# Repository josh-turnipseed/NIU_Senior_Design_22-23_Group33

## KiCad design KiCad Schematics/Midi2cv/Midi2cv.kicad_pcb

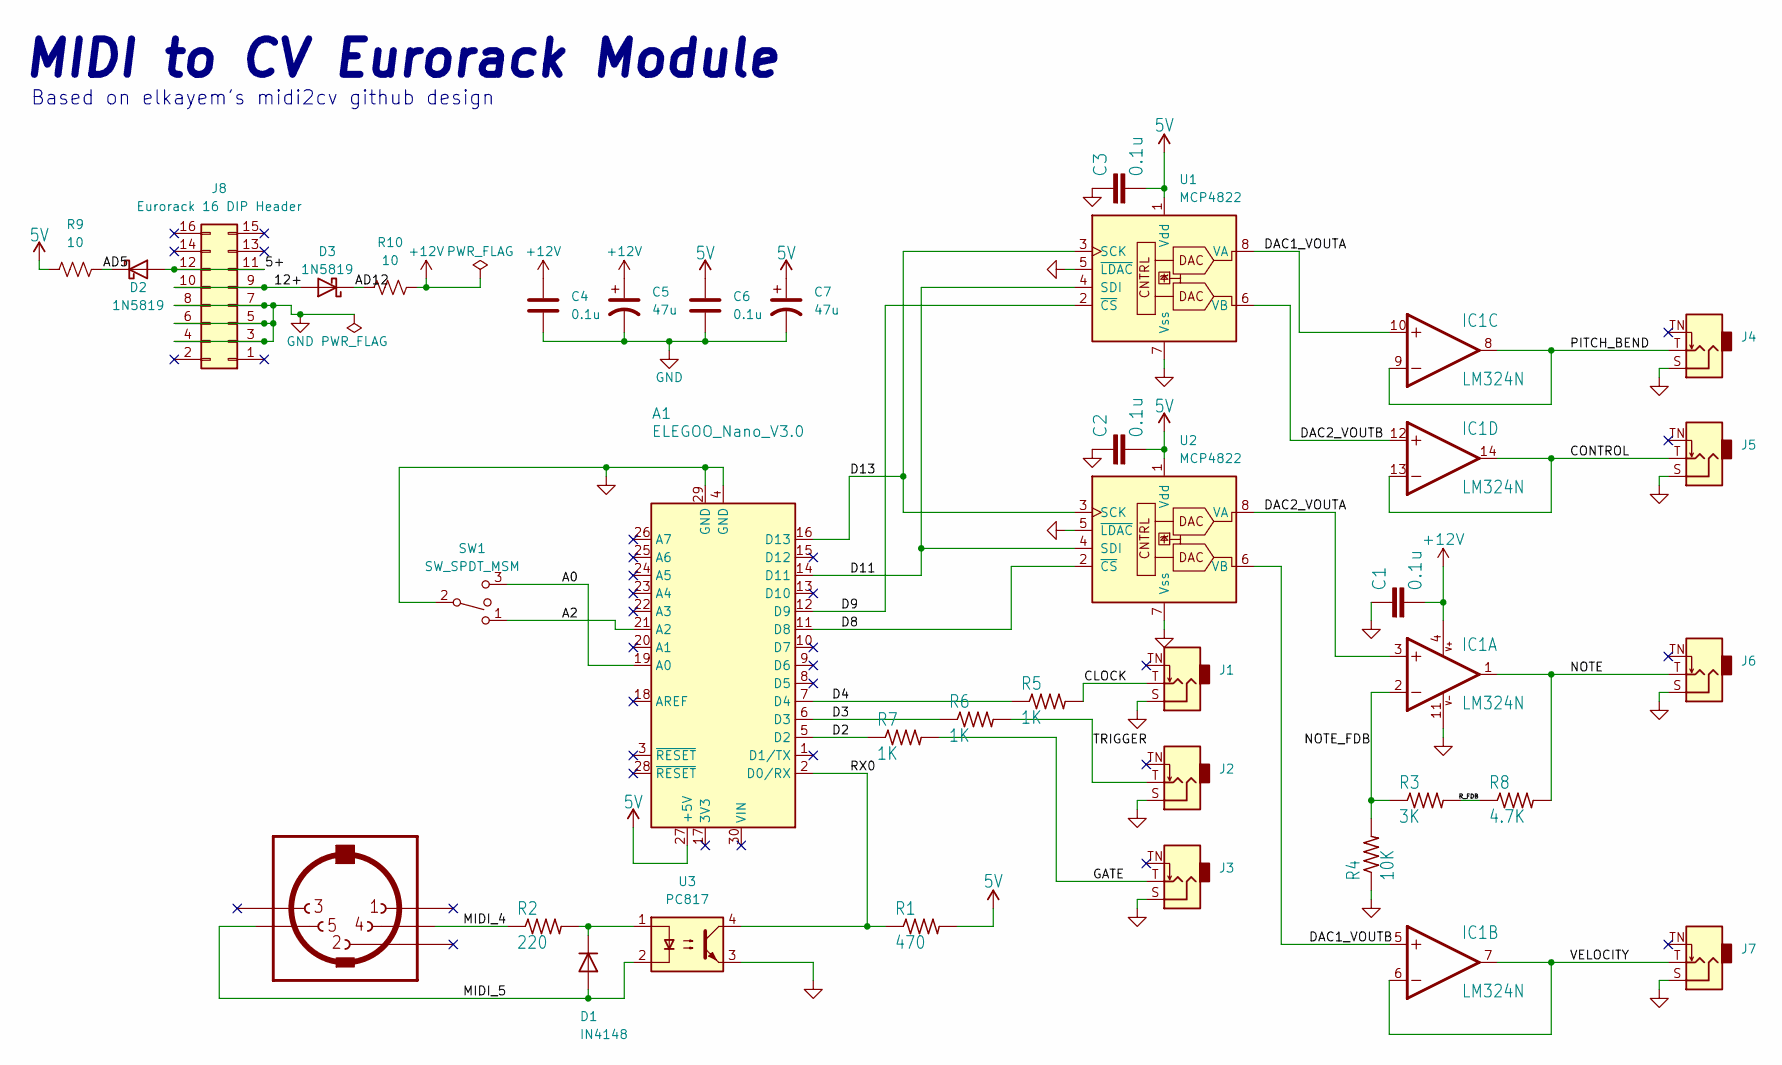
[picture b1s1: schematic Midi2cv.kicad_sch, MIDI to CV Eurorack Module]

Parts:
A1: ELEGOO_Nano_V3.0; Arduino_Nano
C1, C2, C3, C4, C6: 0.1u; C_Disc_D4.7mm_W2.5mm_P5.00mm
C5, C7: 47u; CP_Radial_D4.0mm_P1.50mm
D1: IN4148; D_DO-35_SOD27_P7.62mm_Horizontal
D2, D3: 1N5819; D_DO-41_SOD81_P10.16mm_Horizontal
IC1: LM324N; DIP-14_W7.62mm
J1: Clock; Jack_3.5mm_QingPu_WQP-PJ398SM_Vertical_CircularHoles
J2: Trigger; Jack_3.5mm_QingPu_WQP-PJ398SM_Vertical_CircularHoles
J3: Gate; Jack_3.5mm_QingPu_WQP-PJ398SM_Vertical_CircularHoles
J4: Pitch Bend; Jack_3.5mm_QingPu_WQP-PJ398SM_Vertical_CircularHoles
J5: Continuous Control; Jack_3.5mm_QingPu_WQP-PJ398SM_Vertical_CircularHoles
J6: Note; Jack_3.5mm_QingPu_WQP-PJ398SM_Vertical_CircularHoles
J7: Velocity; Jack_3.5mm_QingPu_WQP-PJ398SM_Vertical_CircularHoles
J8: Eurorack 16 DIP Header; Eurorack_16_pin_header
R1: 470; R_Axial_DIN0207_L6.3mm_D2.5mm_P7.62mm_Horizontal
R2: 220; R_Axial_DIN0207_L6.3mm_D2.5mm_P7.62mm_Horizontal
R3: 3K; R_Axial_DIN0207_L6.3mm_D2.5mm_P7.62mm_Horizontal
R4: 10K; R_Axial_DIN0207_L6.3mm_D2.5mm_P7.62mm_Horizontal
R5, R6, R7: 1K; R_Axial_DIN0207_L6.3mm_D2.5mm_P7.62mm_Horizontal
R8: 4.7K; R_Axial_DIN0207_L6.3mm_D2.5mm_P7.62mm_Horizontal
R9, R10: 10; R_Axial_DIN0207_L6.3mm_D2.5mm_P7.62mm_Horizontal
SW1: SW_SPDT_MSM; SPDT toggle on-off-on
U1, U2: MCP4822; DIP-8_W7.62mm
U3: PC817; DIP-4_W7.62mm
U$1: MIDIJACK; CUI_SD-50BV

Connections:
5V: A1.27 (+5V), C2.2, C3.2, C6.2, C7.1, R1.2, R9.2, U1.1 (Vdd), U2.1 (Vdd)
+12V: C1.2, C4.2, C5.1, IC1.4 (V+), R10.1
/5+: D2.2 (A), J8.11, J8.12
/12+: D3.2 (A), J8.9, J8.10
/A0: A1.19 (A0), SW1.3
/A2: A1.21 (A2), SW1.1
/AD5: D2.1 (K), R9.1
/AD12: D3.1 (K), R10.2
/CLOCK: J1.T, R5.2
/CONTROL: IC1.13 (-IN), IC1.14 (OUT), J5.T
/D2: A1.5 (D2), R7.1
/D3: A1.6 (D3), R6.1
/D4: A1.7 (D4), R5.1
/D8: A1.11 (D8), U2.2 (~CS)
/D9: A1.12 (D9), U1.2 (~CS)
/D11: A1.14 (D11), U1.4 (SDI), U2.4 (SDI)
/D13: A1.16 (D13), U1.3 (SCK), U2.3 (SCK)
/DAC1_VOUTA: IC1.10 (+IN), U1.8 (VA)
/DAC1_VOUTB: IC1.5 (+IN), U2.6 (VB)
/DAC2_VOUTA: IC1.3 (+IN), U2.8 (VA)
/DAC2_VOUTB: IC1.12 (+IN), U1.6 (VB)
/GATE: J3.T, R7.2
/MIDI_4: R2.1, U$1.4
/MIDI_5: D1.2 (A), U3.2, U$1.5
/NOTE: IC1.1 (OUT), J6.T, R8.2
/NOTE_FDB: IC1.2 (-IN), R3.1, R4.2
/PITCH_BEND: IC1.8 (OUT), IC1.9 (-IN), J4.T
/RX0: A1.2 (D0/RX), R1.1, U3.4
/R_FDB: R3.2, R8.1
/TRIGGER: J2.T, R6.2
/VELOCITY: IC1.6 (-IN), IC1.7 (OUT), J7.T
GND: A1.4 (GND), A1.29 (GND), C1.1, C2.1, C3.1, C4.1, C5.2, C6.1, C7.2, IC1.11 (V-), J1.S, J2.S, J3.S, J4.S, J5.S, J6.S, J7.S, J8.3, J8.4, J8.5, J8.6, J8.7, J8.8, R4.1, SW1.2, U1.5 (~LDAC), U1.7 (Vss), U2.5 (~LDAC), U2.7 (Vss), U3.3
unnamed: D1.1 (K), R2.2, U3.1

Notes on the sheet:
Based on elkayem's midi2cv github design
MIDI to CV Eurorack Module

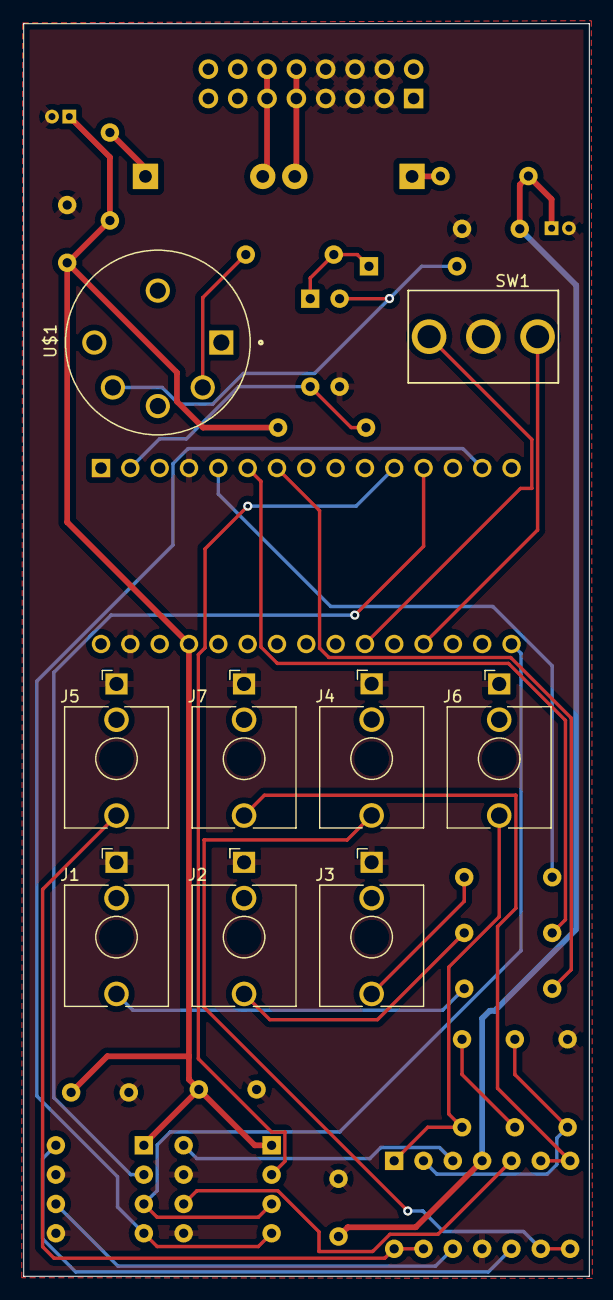
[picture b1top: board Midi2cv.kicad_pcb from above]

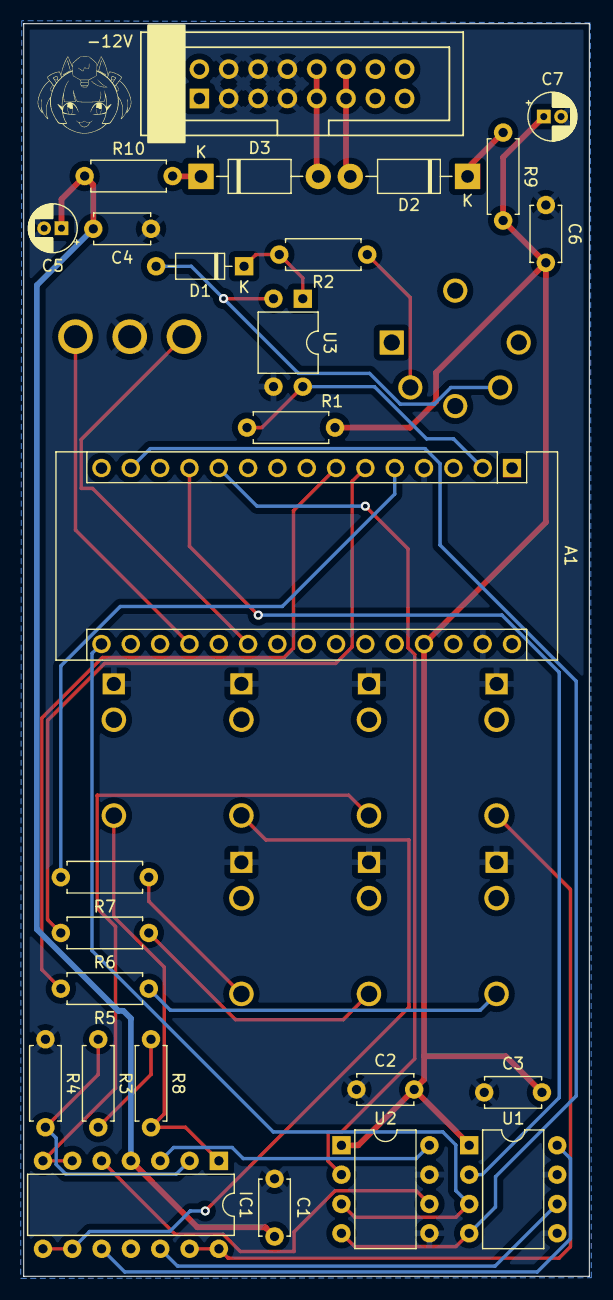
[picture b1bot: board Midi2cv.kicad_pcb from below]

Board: 2 copper layers, 49.0 x 108.5 mm, 35 parts (26 on the bottom side), 33 nets.

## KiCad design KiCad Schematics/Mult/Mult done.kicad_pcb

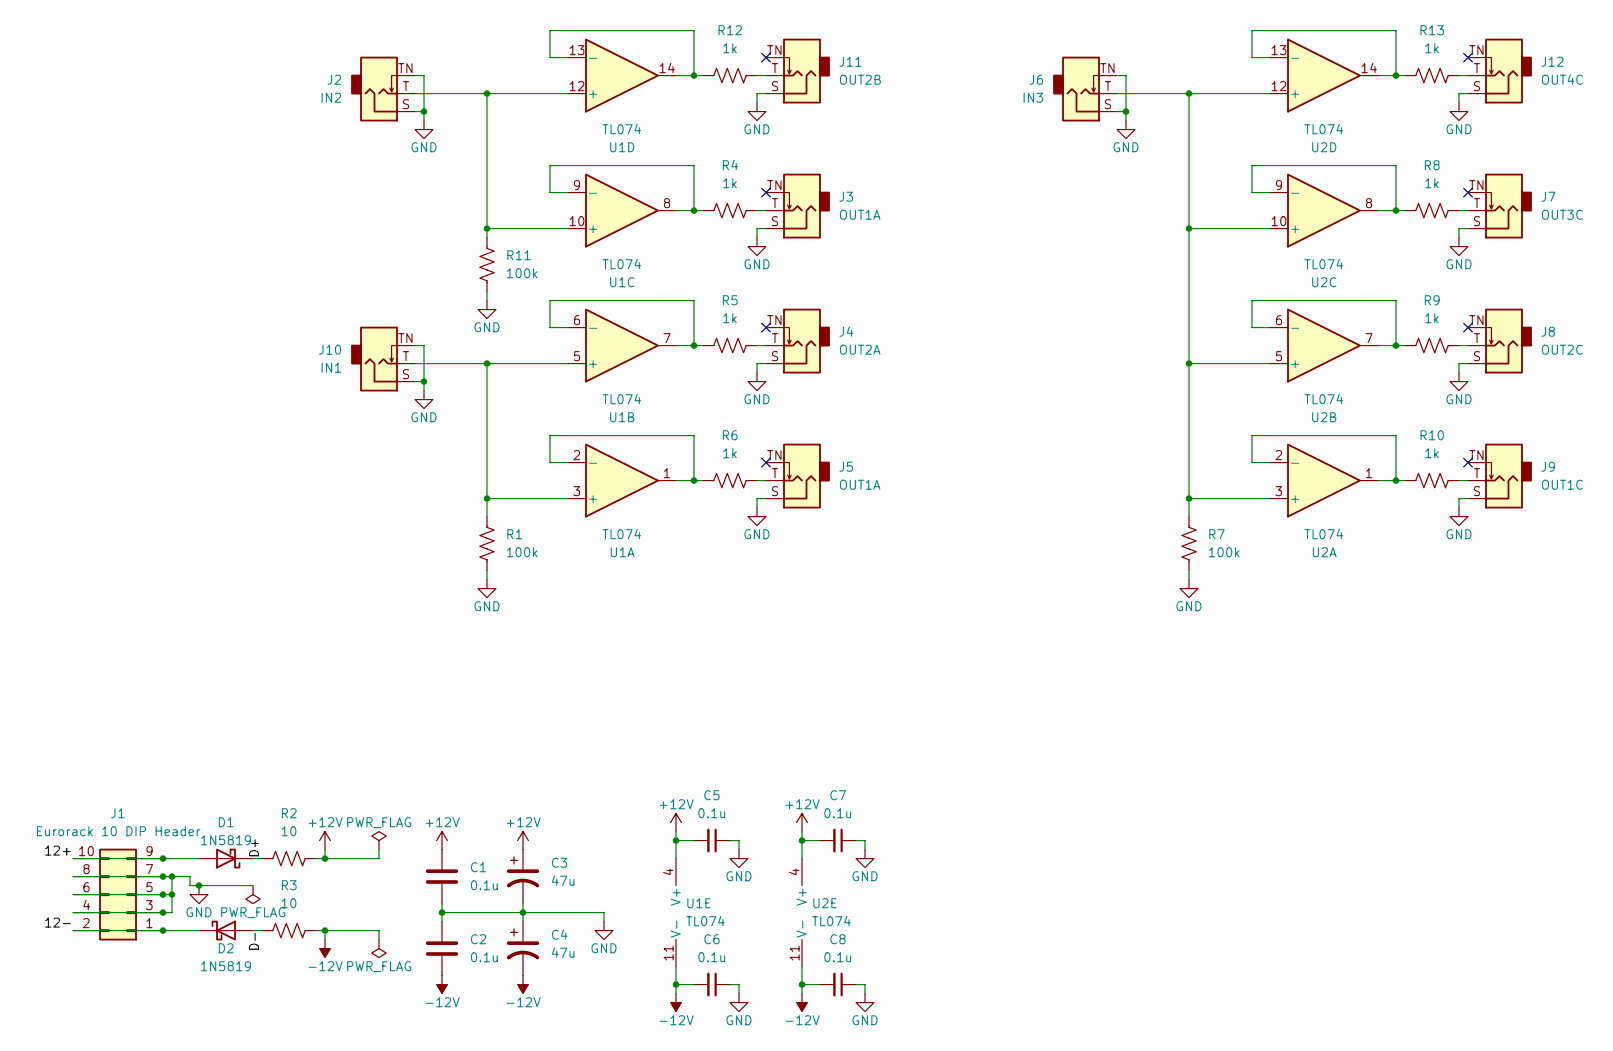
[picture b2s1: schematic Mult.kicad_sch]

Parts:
C1, C2, C5, C6, C7, C8: 0.1u; C_Disc_D4.7mm_W2.5mm_P5.00mm
C3, C4: 47u; CP_Radial_D4.0mm_P2.00mm
D1, D2: 1N5819; D_DO-41_SOD81_P10.16mm_Horizontal
J1: Eurorack 10 DIP Header; Eurorack_10_pin_header
J2: IN2; Jack_3.5mm_QingPu_WQP-PJ398SM_Vertical_CircularHoles
J3, J5: OUT1A; Jack_3.5mm_QingPu_WQP-PJ398SM_Vertical_CircularHoles
J4: OUT2A; Jack_3.5mm_QingPu_WQP-PJ398SM_Vertical_CircularHoles
J6: IN3; Jack_3.5mm_QingPu_WQP-PJ398SM_Vertical_CircularHoles
J7: OUT3C; Jack_3.5mm_QingPu_WQP-PJ398SM_Vertical_CircularHoles
J8: OUT2C; Jack_3.5mm_QingPu_WQP-PJ398SM_Vertical_CircularHoles
J9: OUT1C; Jack_3.5mm_QingPu_WQP-PJ398SM_Vertical_CircularHoles
J10: IN1; Jack_3.5mm_QingPu_WQP-PJ398SM_Vertical_CircularHoles
J11: OUT2B; Jack_3.5mm_QingPu_WQP-PJ398SM_Vertical_CircularHoles
J12: OUT4C; Jack_3.5mm_QingPu_WQP-PJ398SM_Vertical_CircularHoles
R1, R7, R11: 100k; R_Axial_DIN0207_L6.3mm_D2.5mm_P7.62mm_Horizontal
R2, R3: 10; R_Axial_DIN0207_L6.3mm_D2.5mm_P7.62mm_Horizontal
R4, R5, R6, R8, R9, R10, R12, R13: 1k; R_Axial_DIN0207_L6.3mm_D2.5mm_P7.62mm_Horizontal
U1, U2: TL074; DIP-14_W7.62mm

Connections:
+12V: C1.2, C3.1, C5.2, C7.2, R2.1, U1.4 (V+), U2.4 (V+)
-12V: C2.1, C4.2, C6.2, C8.2, R3.1, U1.11 (V-), U2.11 (V-)
/12+: D1.2 (A), J1.9, J1.10
/12-: D2.1 (K), J1.1, J1.2
/D+: D1.1 (K), R2.2
/D-: D2.2 (A), R3.2
GND: C1.1, C2.2, C3.2, C4.1, C5.1, C6.1, C7.1, C8.1, J1.3, J1.4, J1.5, J1.6, J1.7, J1.8, J2.S, J2.TN, J3.S, J4.S, J5.S, J6.S, J6.TN, J7.S, J8.S, J9.S, J10.S, J10.TN, J11.S, J12.S, R1.2, R7.2, R11.2
unnamed: J2.T, R11.1, U1.10 (+), U1.12 (+)
unnamed: J3.T, R4.2
unnamed: J4.T, R5.2
unnamed: J5.T, R6.2
unnamed: J6.T, R7.1, U2.3 (+), U2.5 (+), U2.10 (+), U2.12 (+)
unnamed: J7.T, R8.2
unnamed: J8.T, R9.2
unnamed: J9.T, R10.2
unnamed: J10.T, R1.1, U1.3 (+), U1.5 (+)
unnamed: J11.T, R12.2
unnamed: J12.T, R13.2
unnamed: R4.1, U1.8, U1.9 (-)
unnamed: R5.1, U1.6 (-), U1.7
unnamed: R6.1, U1.1, U1.2 (-)
unnamed: R8.1, U2.8, U2.9 (-)
unnamed: R9.1, U2.6 (-), U2.7
unnamed: R10.1, U2.1, U2.2 (-)
unnamed: R12.1, U1.13 (-), U1.14
unnamed: R13.1, U2.13 (-), U2.14

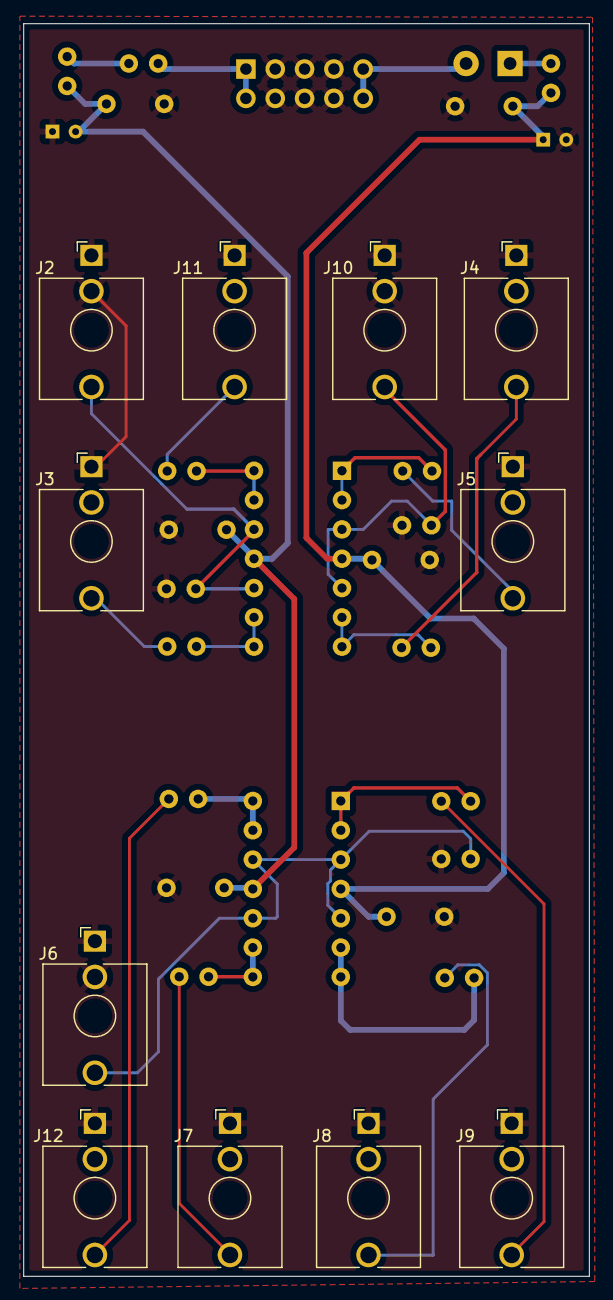
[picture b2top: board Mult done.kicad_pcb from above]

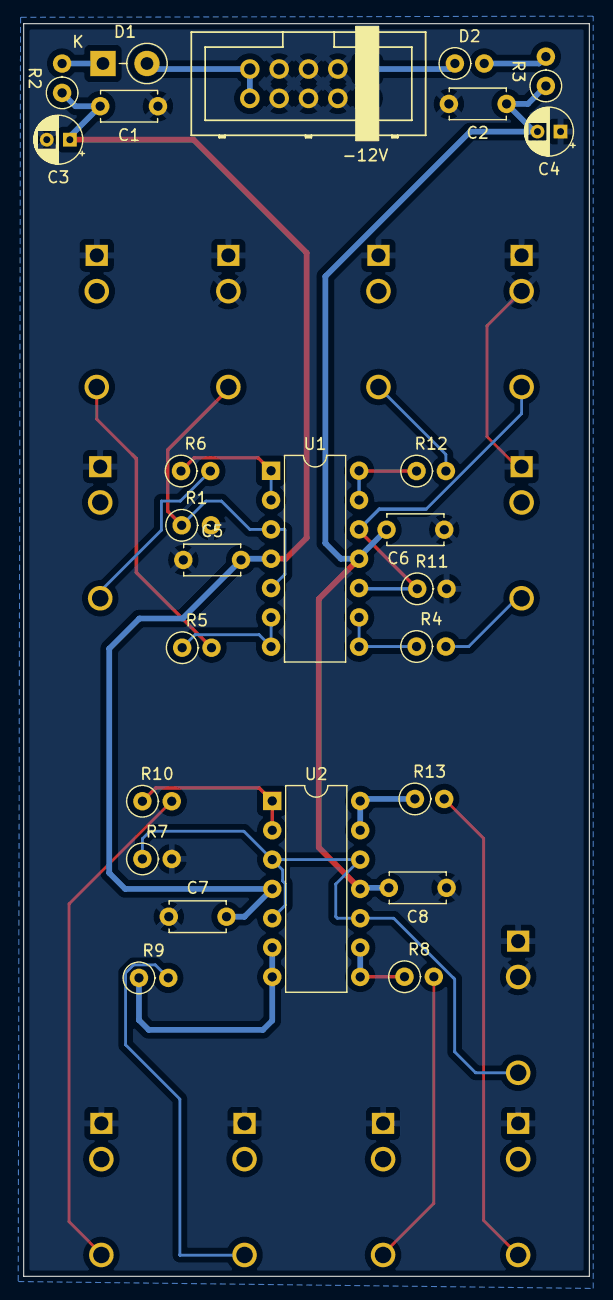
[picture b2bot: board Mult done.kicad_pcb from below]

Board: 2 copper layers, 49.0 x 108.5 mm, 37 parts (26 on the bottom side), 26 nets.

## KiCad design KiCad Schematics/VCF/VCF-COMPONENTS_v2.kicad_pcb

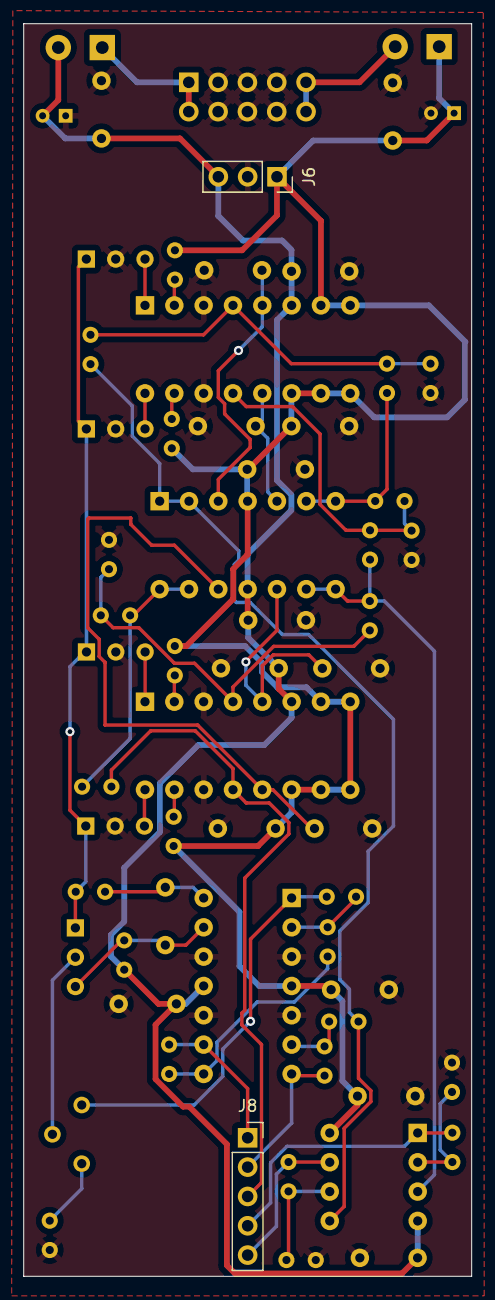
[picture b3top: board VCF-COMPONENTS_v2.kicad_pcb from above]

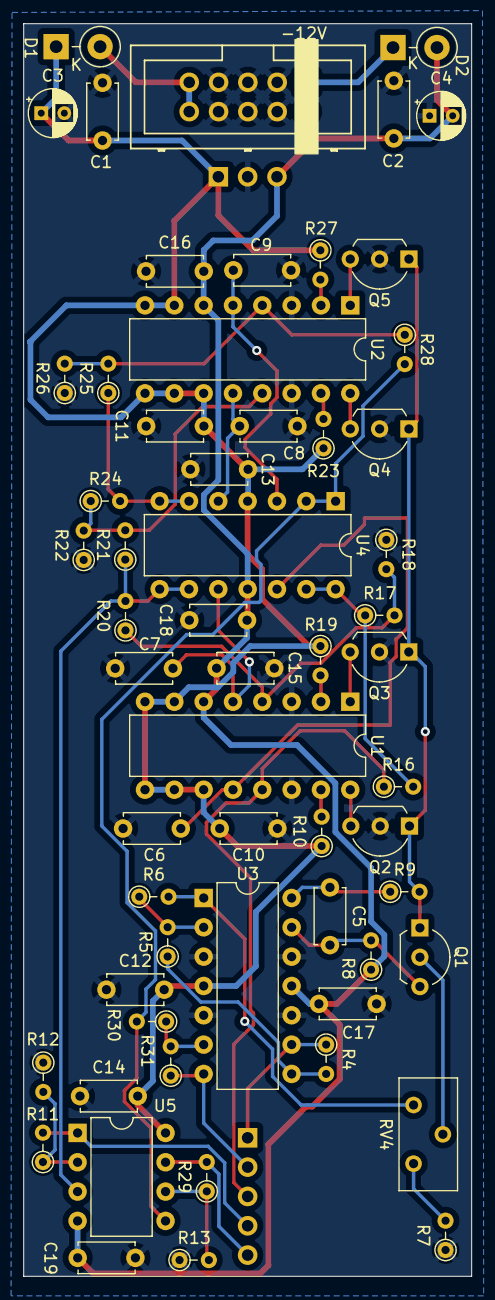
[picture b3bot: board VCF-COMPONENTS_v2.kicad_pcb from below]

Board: 2 copper layers, 38.8 x 108.5 mm, 61 parts (59 on the bottom side), 40 nets.

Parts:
C1, C2, C10, C11, C12, C13, C14, C15, C16, C17, C18, C19: 0.1u; C_Disc_D4.7mm_W2.5mm_P5.00mm
C3, C4: 47u; CP_Radial_D4.0mm_P2.00mm
C5: 20p; C_Disc_D4.7mm_W2.5mm_P5.00mm
C6, C7, C8, C9: 100p; C_Disc_D4.7mm_W2.5mm_P5.00mm
D1, D2: 1N5819; D_DO-41_SOD81_P3.81mm_Vertical_KathodeUp
J1: Eurorack 10 DIP Header; Eurorack_10_pin_header
J6: Comp1; PinSocket_1x03_P2.54mm_Vertical
J8: Comp2; PinSocket_1x05_P2.54mm_Vertical
Q1, Q2, Q3, Q4, Q5: 2N3906; TO-92L_Inline_Wide
R4, R5, R12, R13, R16, R17, R20, R21, R24, R25, R28, R31: 100k; R_Axial_DIN0204_L3.6mm_D1.6mm_P2.54mm_Vertical
R6: 1.87k; R_Axial_DIN0204_L3.6mm_D1.6mm_P2.54mm_Vertical
R7: 470; R_Axial_DIN0204_L3.6mm_D1.6mm_P2.54mm_Vertical
R8: 1Meg; R_Axial_DIN0204_L3.6mm_D1.6mm_P2.54mm_Vertical
R9: 20k; R_Axial_DIN0204_L3.6mm_D1.6mm_P2.54mm_Vertical
R10, R19, R23, R27: 150k; R_Axial_DIN0204_L3.6mm_D1.6mm_P2.54mm_Vertical
R11: 1.8k; R_Axial_DIN0204_L3.6mm_D1.6mm_P2.54mm_Vertical
R18, R22, R26: 1k; R_Axial_DIN0204_L3.6mm_D1.6mm_P2.54mm_Vertical
R29: 3.9k; R_Axial_DIN0204_L3.6mm_D1.6mm_P2.54mm_Vertical
R30: 10k; R_Axial_DIN0204_L3.6mm_D1.6mm_P2.54mm_Vertical
RV4: 100; Potentiometer_Bourns_3296Y_Vertical
U1, U2: LM13700; DIP-16_W7.62mm
U3, U4: TL074; DIP-14_W7.62mm
U5: TL072; DIP-8_W7.62mm

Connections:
+12V: C1.2, C3.1, C10.2, C11.2, C12.2, C13.2, C14.2, D1.1 (K), J6.1, R10.1, R19.1, R23.1, R27.1, U1.7, U1.8, U1.9, U1.10, U1.11 (V+), U2.7, U2.8, U2.9, U2.10, U2.11 (V+), U3.4 (V+), U4.4 (V+), U5.8 (V+)
-12V: C2.1, C4.2, C15.2, C16.2, C17.2, C18.2, C19.2, D2.2 (A), J6.3, R8.1, U1.6 (V-), U2.6 (V-), U3.11 (V-), U4.11 (V-), U5.4 (V-)
/1V/Oct: R6.2, RV4.1, U3.1
/2P_FDB: R11.1, R12.2, U5.2 (-)
/4P_FDB: R13.2, R29.1, U5.6 (-)
/12+: D1.2 (A), J1.9, J1.10
/12-: D2.1 (K), J1.1, J1.2
/Amp_C1: Q2.3 (C), U1.16
/Amp_C2: Q3.3 (C), U1.1
/Amp_C3: Q4.3 (C), U2.16
/Amp_C4: Q5.3 (C), U2.1
/Bias_Current: C5.2, Q1.3 (C), R8.2, U3.13 (-)
/Buf_Out1: R16.2, R17.1, U4.13 (-), U4.14
/Buf_Out2: R20.2, R21.1, U4.8, U4.9 (-), U5.3 (+)
/Buf_Out3: R24.2, R25.1, U4.6 (-), U4.7
/Buf_Out4: R28.2, R30.2, U4.1, U4.2 (-), U5.5 (+)
/CV_FDB: R4.2, R5.1, U3.8
/CV_SCLE: R5.2, R6.1, U3.2 (-)
/Cout1: C6.2, U1.12, U4.12 (+)
/Cout2: C7.2, U1.5, U4.10 (+)
/Cout3: C8.2, U2.12, U4.5 (+)
/Cout4: C9.2, U2.5, U4.3 (+)
/Exp_Cout: Q1.1 (E), Q2.1 (E), Q3.1 (E), Q4.1 (E), Q5.1 (E), R9.2
/Exp_Out: C5.1, R9.1, U3.14
/INV2: R17.2, R18.2, R20.1, U1.4 (-)
/INV3: R21.2, R22.2, R24.1, U2.13 (-)
/INV4: R25.2, R26.2, R28.1, U2.4 (-)
/Res_INV: R30.1, R31.2, U3.6 (-)
/Trim: R7.2, RV4.3
Audio_1st_invert_Comp: J8.3, R16.1, U1.13 (-)
Audio_-12Out_Comp: J8.4, R11.2, U5.1
Audio_-24Out_Comp: J8.5, R29.2, U5.7
CV_Sum_Comp: J8.1, R4.1, U3.9 (-)
GND: C1.1, C2.2, C3.2, C4.1, C6.1, C7.1, C8.1, C9.1, C10.1, C11.1, C12.1, C13.1, C14.1, C15.1, C16.1, C17.1, C18.1, C19.1, J1.3, J1.4, J1.5, J1.6, J1.7, J1.8, J6.2, Q2.2 (B), Q3.2 (B), Q4.2 (B), Q5.2 (B), R7.1, R12.1, R13.1, R18.1, R22.1, R26.1, U1.3 (+), U1.14 (+), U2.3 (+), U2.14 (+), U3.3 (+), U3.5 (+), U3.10 (+), U3.12 (+)
unnamed: Q1.2 (B), RV4.2
unnamed: R10.2, U1.15 (DIODE_BIAS)
unnamed: R19.2, U1.2 (DIODE_BIAS)
unnamed: R23.2, U2.15 (DIODE_BIAS)
unnamed: R27.2, U2.2 (DIODE_BIAS)
Res_Comp: J8.2, R31.1, U3.7
